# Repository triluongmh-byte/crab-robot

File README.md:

# 🦀 Crab Robot

**An 8-servo crab whose face is a screen with two eyes. Drive it from your phone, or let it walk by itself and dodge obstacles. Play emotions, change the lamp colour.**

[Drive](#open-the-controls) · [Tự đi (Auto)](#tự-đi-auto-mode) · [Gaits](#gaits-and-sliders) · [Emotions](#emotions) · [Calibration](#calibration-ráp) · [Servo channels](#which-servo-goes-where) · [Wiring](#wiring) · [Firmware](#firmware)

| Idle: eyes open, blink, glance | Walking: happy eyes ^ ^ |
|---|---|
|  |  |

*Photos and video by the owner, 14 Nov 2026, firmware `positional180-v19`.*

The web controls are in Vietnamese. Button names below are quoted as they appear on screen, with the English meaning next to them.

## What's on the crab

| Part | How to spot it | Job |
|---|---|---|
| **LILYGO T-Display-S3** (non-touch) | Black board with the screen and USB-C port | Wi-Fi, web controls, the eyes |
| **PCA9685** | Blue board with 16 rows of 3-pin headers | Servo pulses for CH0–CH7 |
| **8 × SG90 positional 180°** | 4 hips on the body, 4 knees on the legs | Joints. **Do not use 360° continuous servos** |
| **WS2812 strip ×8** | Thin strip with 8 LEDs | Colour lamp |
| **2 × HC-SR04P** (round 1, optional) | Two ultrasonic "eyes" at the front | Obstacle sensing for **Tự đi** (Auto) |
| **Separate 5 V servo supply** | Into the PCA `V+` / `GND` screw terminal | Powers servos and LEDs; kept apart from the LILYGO's USB |

## Open the controls

1. Power it on. The servos **arm themselves** one channel at a time over about 3 seconds, then the crab stands up. Keep fingers out from between the legs.
2. Read the **small line at the bottom of the screen**:
   - On home Wi-Fi: the line shows the address, e.g. `Đã vào Wi-Fi  192.168.x.x` ("joined Wi-Fi"). Open that address on a phone on the same network.
   - Not on home Wi-Fi: join the crab's own network **`CuaRobot-XXXX`** (no password) and open **http://192.168.4.1/**.
   - Never saved a Wi-Fi network: the screen shows a QR code to join quickly.
3. Hold a button to walk, release to stop: **↑ Tiến** (forward) · **← Trái** (left) · **Phải →** (right) · **↓ Lùi** (back). If the link drops, the crab stops within 0.5 s.
4. To forget the saved Wi-Fi, hold **BOOT** for about 8 seconds.

On the phone, tap **☰** for settings. The **Trạng thái** (status) tab lists firmware, PCA9685, servos, gait, speed, lamp and Wi-Fi.

## Tự đi (Auto mode)

Needs the two front ultrasonic sensors (round 1 in [firmware/BATTERY-AUTONOMY.md](firmware/BATTERY-AUTONOMY.md)): left on GPIO10/11, right on GPIO12/13.

1. Arm the servos as usual. When both sensors answer, the green **🤖 Tự đi** button above the pad lights up, and the line beside it shows both distances.
2. Tap **🤖 Tự đi**.
   - The crab walks forward and veers away from things on one side.
   - At an obstacle closer than 25 cm it stops with surprised eyes, backs off turning towards the freer side, and carries on.
   - Now and then it wanders off or stops to look around.
3. **DỪNG** or any drive button takes back control (Manual). So do an emotion, **Ráp** and **BOOT**.

It never starts by itself, even after a reset. If it gets stuck 5 times in a row it stops and shows **Kẹt rồi, nhờ giúp** with sad eyes. Locking the phone doesn't stop it; only DỪNG does.

## Gaits and sliders

| Gait | How it moves | When to use it |
|---|---|---|
| **Chéo** (diagonal, default) | Diagonal leg pairs push in turn, with moments where all 4 feet are down | Steady, doesn't spin. The owner's favourite |
| **Cặp trước/sau** (front/rear pairs) | Front pair pushes, then the rear pair | Old gait, kept for comparison. Sideways walking rotates the body |
| **Búng gối** (knee flick, experimental) | Forward/back: hips swing out (front legs forward, rear legs back), then all 4 knees flick. Left/right still uses the diagonal gait | Experiments |

Sliders in the settings panel:

| Slider | Range | Saved on the crab? | Use it when |
|---|---|---|---|
| **Tốc độ** (speed) | 20–100%, default 90% | No (back to 90% at boot) | You want to walk slowly to watch |
| **Độ nhấc gối** (knee lift) | 20–60°, default 45° | Yes | Feet drag on the table while the hips swing back: raise it |
| **Bù lệch trái ↔ phải** (heading trim) | −30 … +30% | Yes | Drifts right walking forward: move towards **+**; drifts left: towards **−** |
| **Góc hông búng** (flick hip angle) | 30–90°, only shown for Búng gối | No | Legs touch each other: lower it |
| **Lamp colour** | Colour picker next to **Bật / tắt đèn** (lamp on/off) | Yes | Changes the LED strip colour |

Angles on the page are **nominal command angles**, not measured ones. On the usual SG90 scale, 1° nominal is about ½° real.

## Emotions

Tap **🎭 Cảm xúc** at the top of the main page, or open `/emo`.

- **7 built-in emotions:** 😄 happy, 😢 sad, 😡 angry, 👋 hello, 💃 dance, 😴 sleep, 😲 surprised. Each has its own lamp colour.
- **Make your own:** drag a leg's Hip/Knee sliders and the crab follows live. Tick **Đối xứng trái/phải** (mirror left/right) to make both sides match. Add frames, set move/hold times, name it and tap **Lưu vào cua** (save to crab).
- **Slider direction:** Hip **+** moves the foot forward. Knee **+** lifts the leg, **−** pushes down (body goes up).
- **Safety:** leaving the page or losing the link returns the crab to its standing pose, slowly at 120°/s.

## The eye screen

Two white eyes on black, drawn from shapes in the style of the Claude pet:

- **Idle:** blinks every 2.5–5.5 s and glances left/right now and then.
- **Walking or playing an emotion:** happy eyes ^ ^.
- **Bottom line:** Wi-Fi state and address on one row. If both don't fit, only the address is shown. PCA9685 wiring errors show here too.

## Calibration (Ráp)

Open **☰ → Ráp** (assembly). Assembly mode locks the drive buttons.

1. Tap **Tư thế đứng** (standing pose).
2. For each hip, tap **±3** until the leg sits at an even diagonal, then fine-tune with **±1**. A ±1 step is close to the SG90 deadband, so the servo may not move on the first tap.
3. For each knee, adjust until all 4 feet touch the floor and the body is level.
4. Tap **Lưu tâm** (save centres), then **Xong ráp** (done). Without Lưu tâm the trims are lost at reboot.

Trims max out at ±30°. If a channel is at ±30°, pull the horn off and refit it one spline over (about 14°) to bring the trim back near 0.

Replacing a servo:
1. Unplug the 5 V supply and remove the horn.
2. Plug it back in, go to **Ráp → Giữa thô · 1500 µs** (rough centre), wait about 3 seconds.
3. Fit the horn so the leg sits on the diagonal.
4. Set that channel's trim back to 0, tune it again, then **Lưu tâm**.

## Which servo goes where?

**One servo = one 3-wire plug = one CH socket.** Hips sit on the body, knees on the legs. Leg names on the Ráp and Cảm xúc pages follow this table:

| Leg | Hip | Knee |
|---|---|---|
| Front left | **CH0** | CH1 |
| Front right | **CH2** | CH3 |
| Rear left | **CH4** | CH5 |
| Rear right | **CH6** | CH7 |

> ⚠️ **Walking direction and leg names are set separately.** The owner turned the crab around, so **Tiến** (forward) walks towards the **CH4/CH6** end (`cfg::FRONT_IS_CH46 = true` in `firmware/crab/config.h`). If forward/back/left/right are all reversed, flip that constant and reflash.

At each socket: **orange → `PWM`/`S`**, **red (middle) → `V+`**, **brown → `GND`/`−`**. Check the GND label printed on the board before plugging in. Leave CH8–CH15 empty.

## Wiring

**Unplug both supplies before changing any wire.**

| Lead | LILYGO pin | Other end |
|---|---|---|
| **A** | `3V` | PCA **`VCC`**, 3.3 V logic |
| **B** | `G` / `GND` | PCA **`GND`** |
| **C** | `18` | PCA **`SDA`** |
| **D** | `17` | PCA **`SCL`** |
| **E** | `1` | LED **`DIN`** |

**Power:**
- **USB:** into the LILYGO's USB-C. Use a data cable when flashing.
- **Separate 5 V:** into the PCA terminal, positive to **`V+`**, negative to **`GND`**.
- **LEDs:** powered from the PCA's servo-side **`V+`/`GND`**.

**`VCC` is 3.3 V logic; `V+` is the 5 V servo supply. Never join them, and never power servos from the LILYGO.** Close-up photos and troubleshooting are in the [wiring guide](firmware/WIRING.md).

## Saving and restoring settings

The owner's tuned settings are in [`firmware/settings/owner-2026-11-13.json`](firmware/settings/owner-2026-11-13.json): trims for all 8 channels, speed, knee lift, heading trim, flick hip angle, gait and lamp colour.

After wiping the flash or swapping the board, restore them with:

```sh
python3 tools/firmware/restore_settings.py firmware/settings/owner-2026-11-13.json --host <crab-ip>
```

Add `--dry-run` to preview the requests. The script needs all 8 servos armed, and it takes control away from any open web page (reload the page afterwards).

## Firmware

- **Running now:** `positional180-v22`, target **`lilygo`**. The **`integrated`** target is for the future integrated board.
- **Build, flash and version history:** [firmware/README.md](firmware/README.md). See also [gaits](firmware/CRAWL.md), [web controls](firmware/WEB-CONTROL.md) and [emotions](firmware/EMOTIONS.md).

```sh
# Host-side tests (don't touch the crab)
python3 tools/firmware/check.py core web drivers display http targets
python3 tools/firmware/test_restore_settings.py

# Build both targets (no flashing, no motors)
python3 tools/firmware/build.py --target all
```

Building doesn't flash a board, run motors, print or order anything.

## Known issues

- **Speed, gait and flick hip angle aren't saved on the crab.** A reboot brings back the defaults: 90%, Chéo, 90°.
- **Walking direction and leg names are set separately** (see the warning under [servo channels](#which-servo-goes-where)). Built-in emotions and the heading trim may feel "back to front" relative to Tiến.
- **A USB cable dragging behind** can pull the crab off course. A power bank mounted on the body walks straighter.
- **Knee flick at 90° goes past the body's old clearance** (30/60°). On the first run, watch for legs hitting each other.

## More docs

| Looking for | Open |
|---|---|
| Printed parts, assembly, body edits | [case/README.md](case/README.md) · [printed parts list](case/PRINTED-INVENTORY.md) |
| Sensors and Auto mode (round 1), battery power (round 2) | [firmware/BATTERY-AUTONOMY.md](firmware/BATTERY-AUTONOMY.md) |
| Integrated ESP32-S3 + PCA9685 board | [docs/INTEGRATED-CONTROLLER.md](docs/INTEGRATED-CONTROLLER.md) · [KiCad sources](design/) |
| Build-from-source results | [BUILD-VALIDATION.md](BUILD-VALIDATION.md) |
| 360° servo trials (didn't work out) | [firmware/EXPERIMENT-STATUS.md](firmware/EXPERIMENT-STATUS.md) |

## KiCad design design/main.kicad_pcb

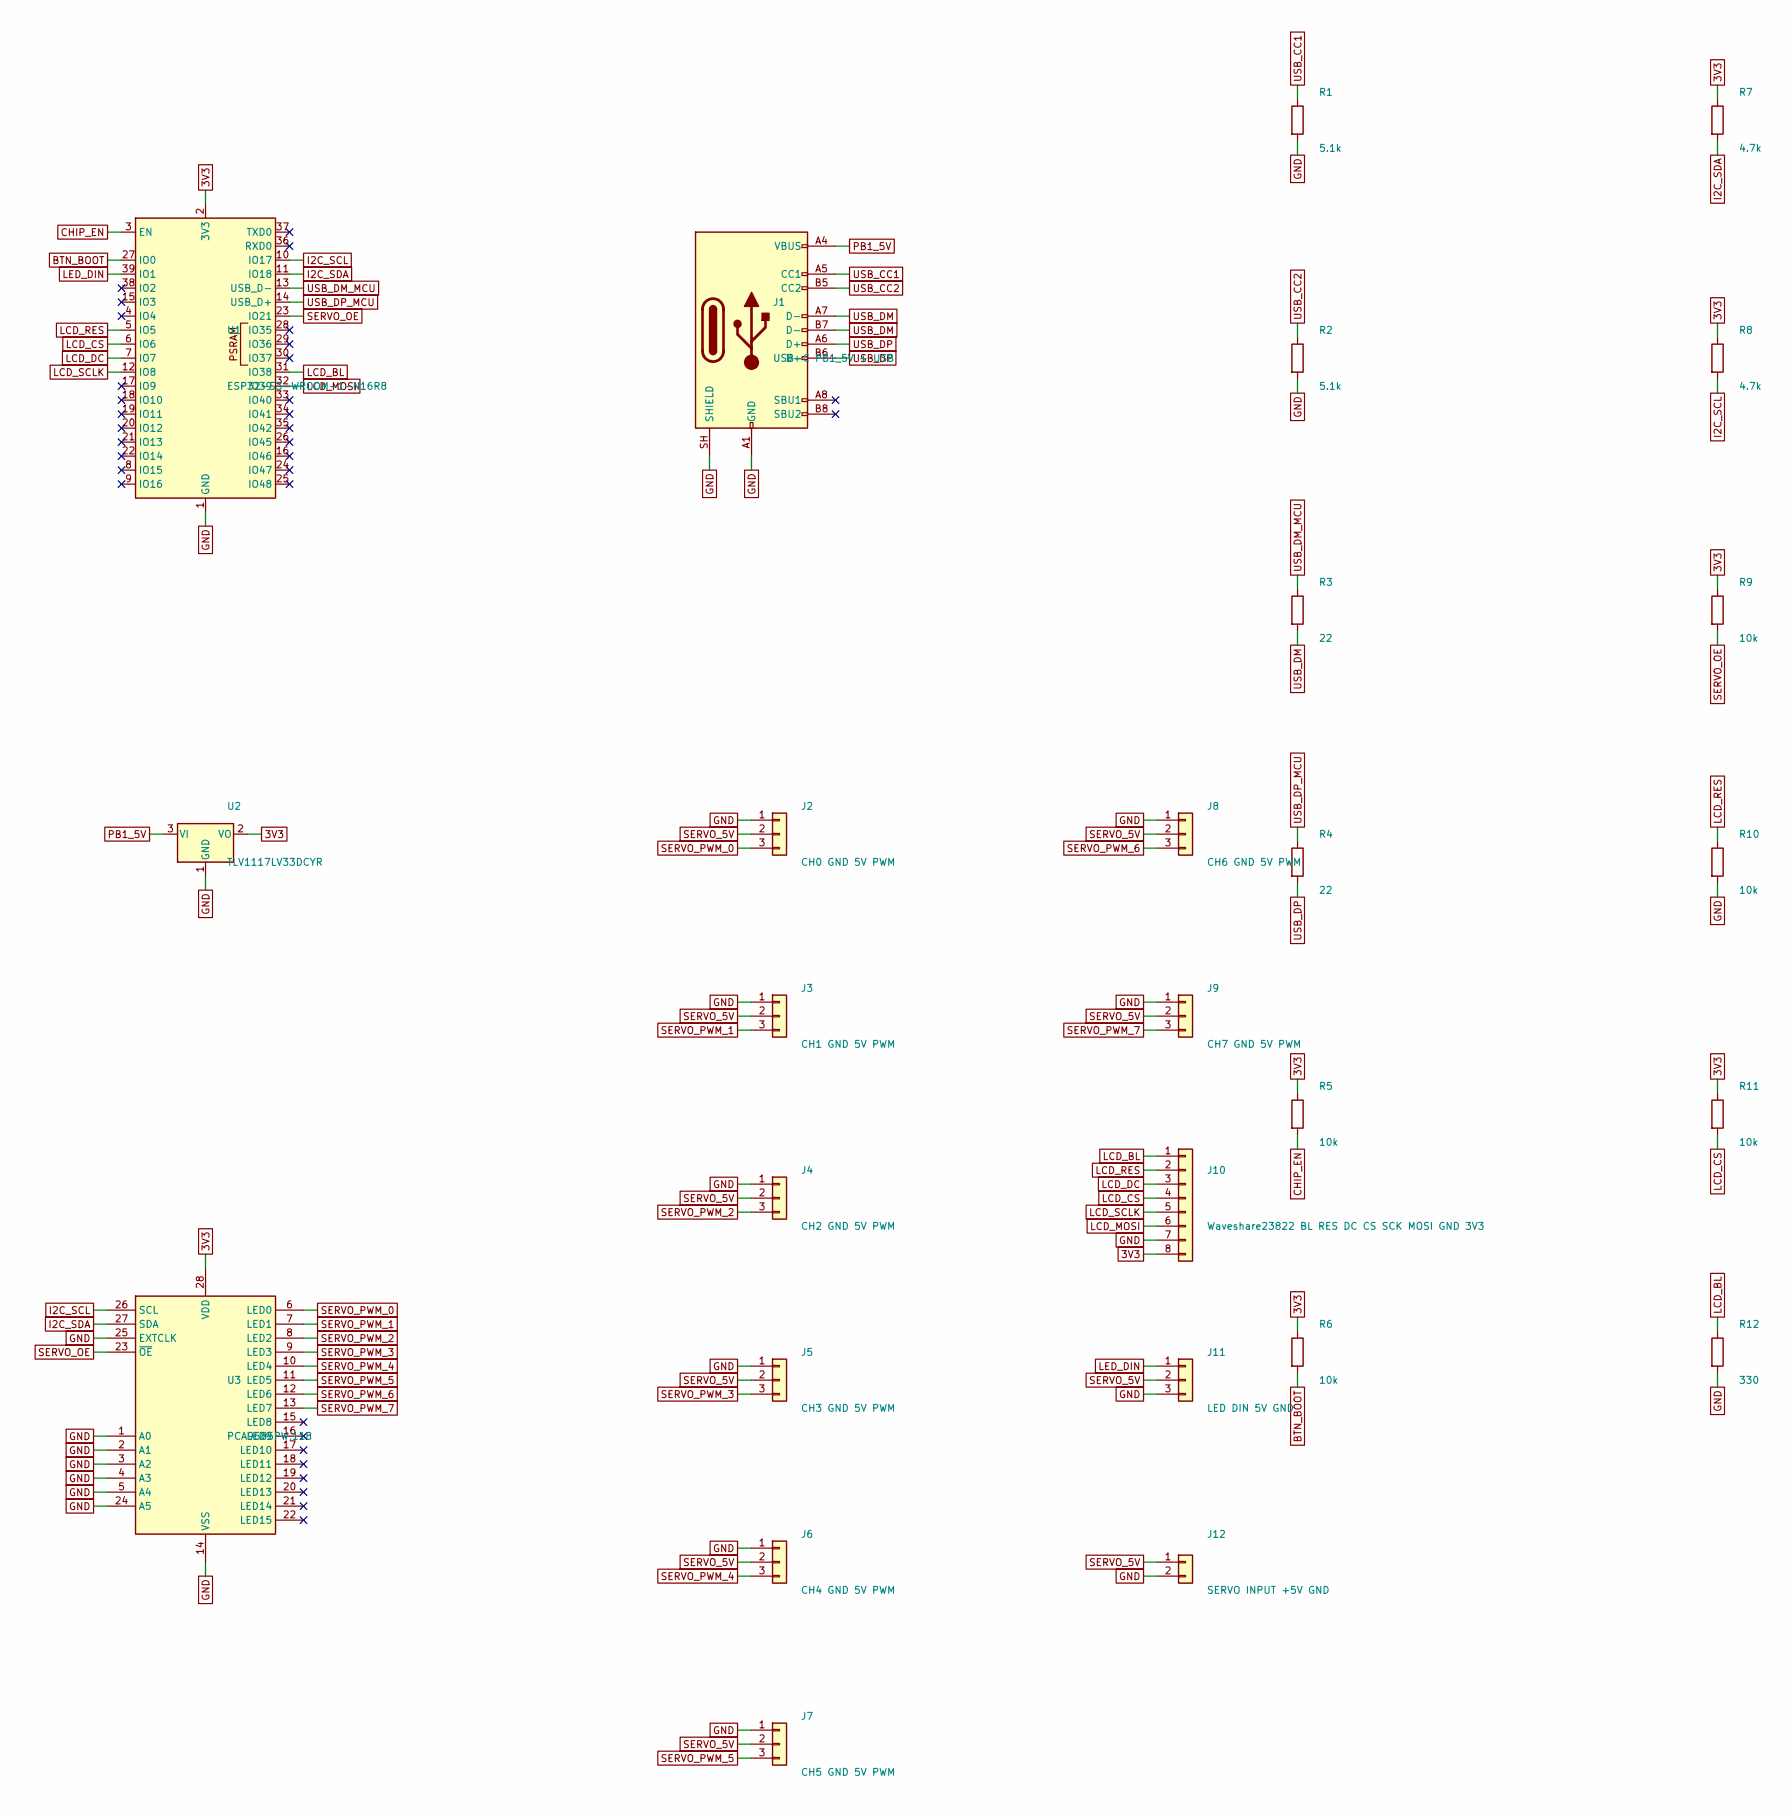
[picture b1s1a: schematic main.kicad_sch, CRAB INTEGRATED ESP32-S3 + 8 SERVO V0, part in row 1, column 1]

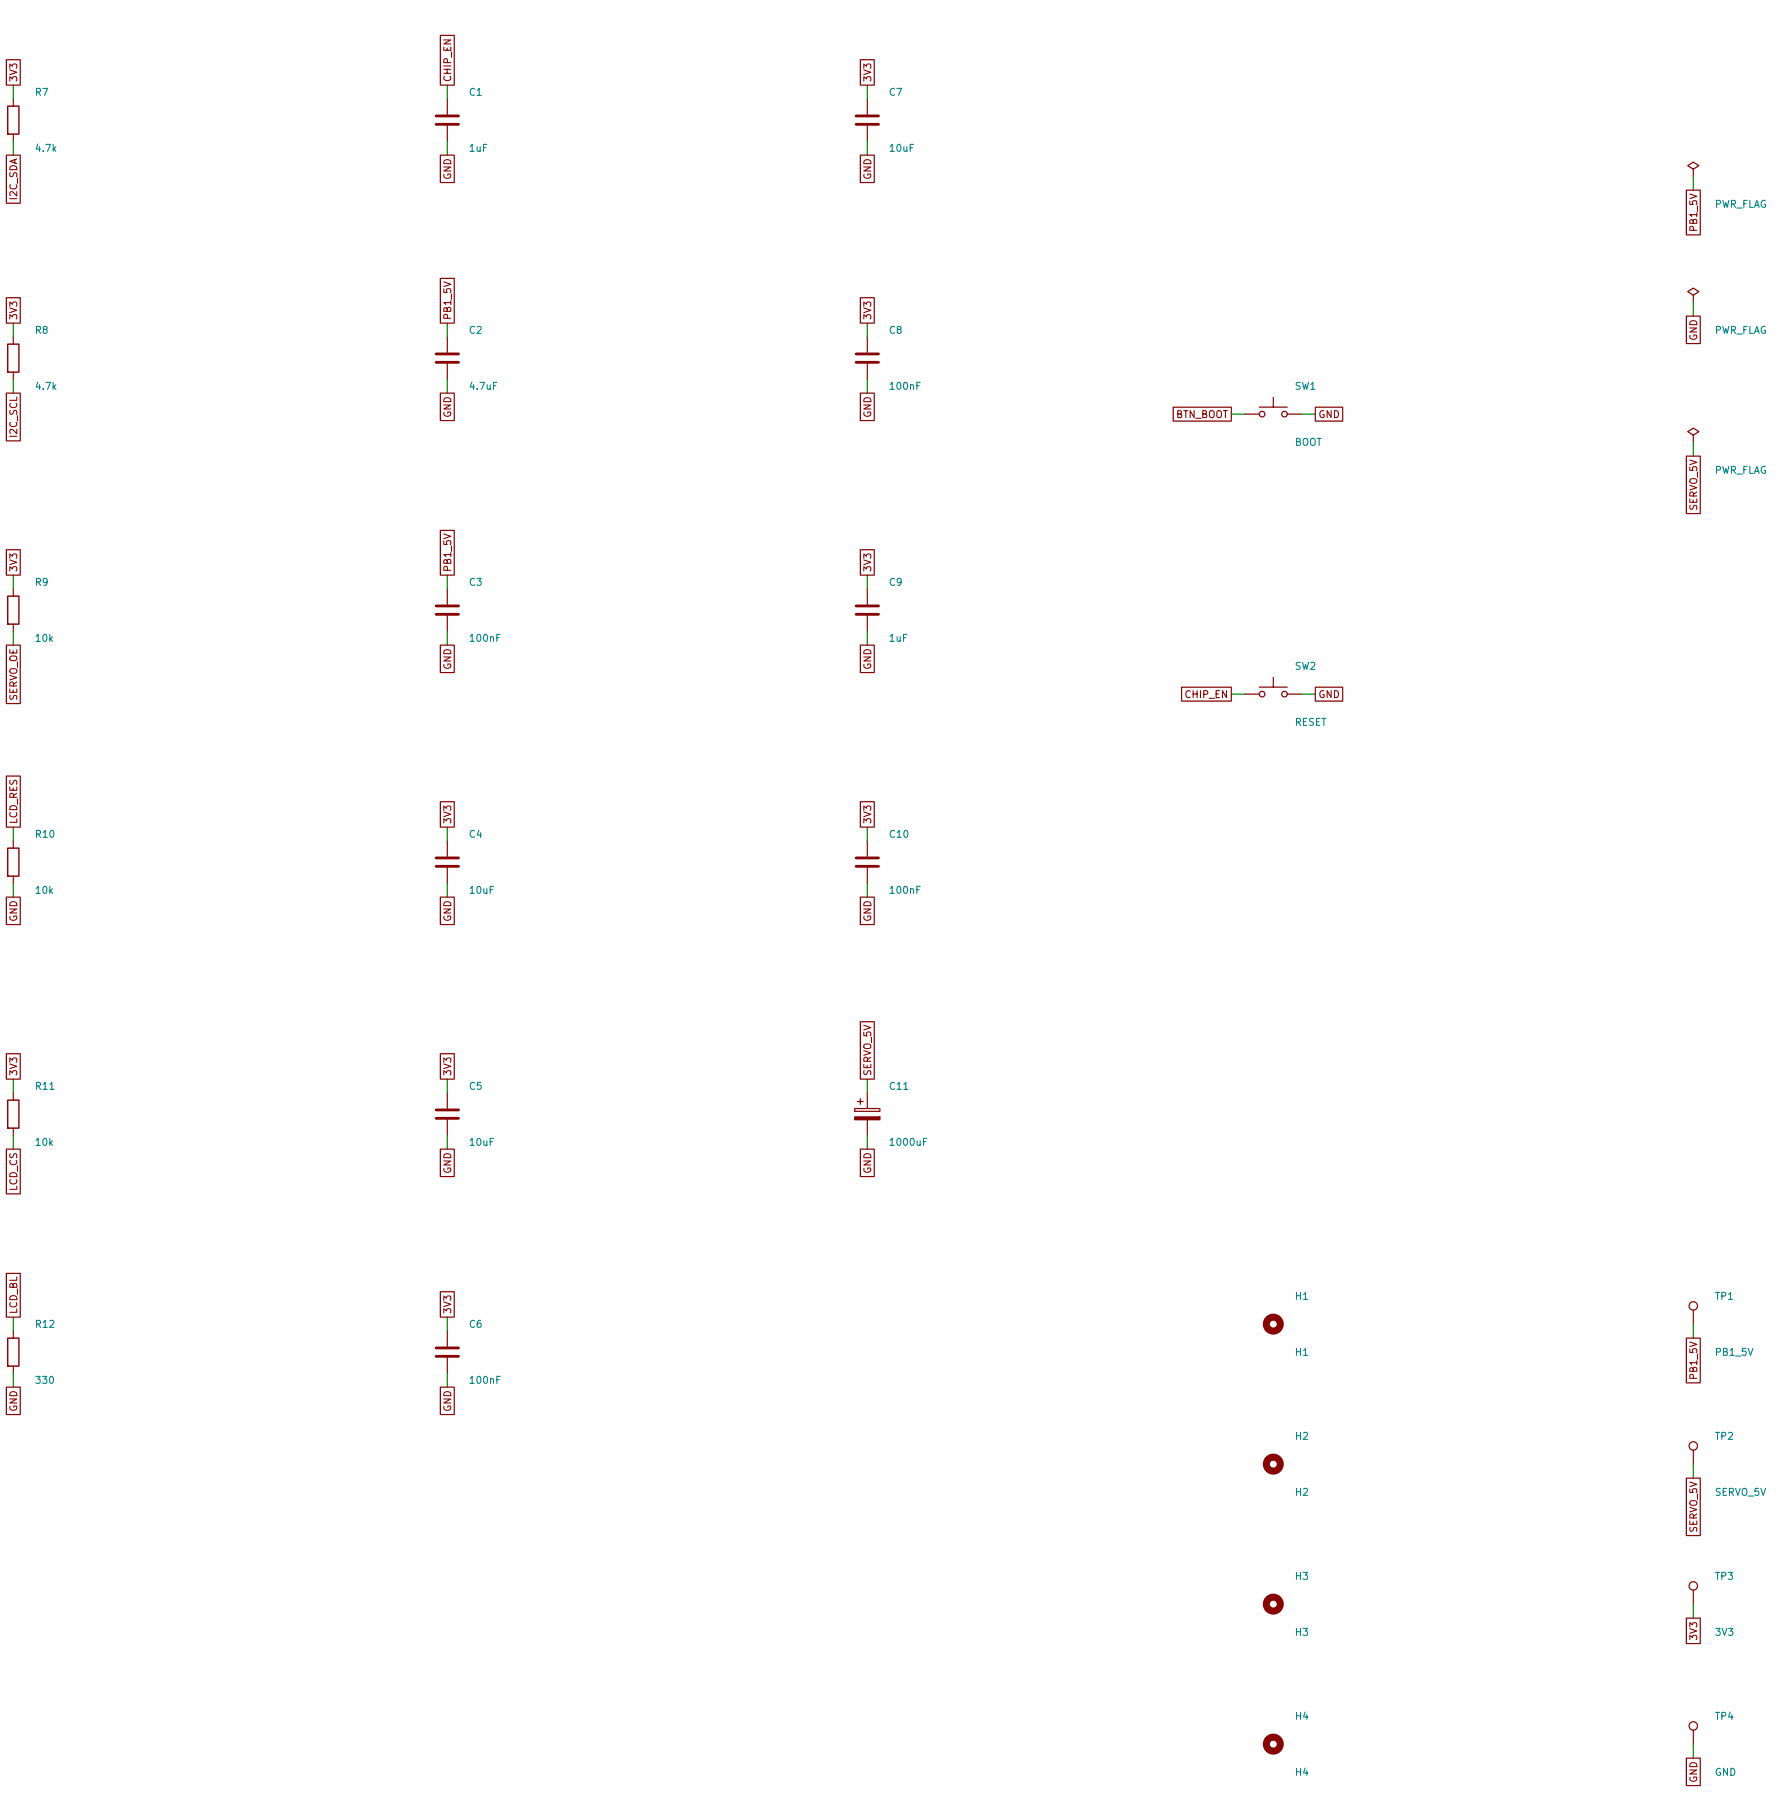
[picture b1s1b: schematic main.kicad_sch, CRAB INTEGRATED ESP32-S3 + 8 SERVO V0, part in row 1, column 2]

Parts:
C1, C9: 1uF; C_0402_1005Metric
C2: 4.7uF; C_0805_2012Metric
C3, C6, C8, C10: 100nF; C_0402_1005Metric
C4, C5, C7: 10uF; C_0805_2012Metric
C11: 1000uF; CP_Elec_10x10
H1: H1; MountingHole_3.2mm_M3
H2: H2; MountingHole_3.2mm_M3
H3: H3; MountingHole_3.2mm_M3
H4: H4; MountingHole_3.2mm_M3
J1: USB-C PB1_5V + USB; USB_C_Receptacle_HRO_TYPE-C-31-M-12
J2: CH0 GND 5V PWM; PinHeader_1x03_P2.54mm_Vertical
J3: CH1 GND 5V PWM; PinHeader_1x03_P2.54mm_Vertical
J4: CH2 GND 5V PWM; PinHeader_1x03_P2.54mm_Vertical
J5: CH3 GND 5V PWM; PinHeader_1x03_P2.54mm_Vertical
J6: CH4 GND 5V PWM; PinHeader_1x03_P2.54mm_Vertical
J7: CH5 GND 5V PWM; PinHeader_1x03_P2.54mm_Vertical
J8: CH6 GND 5V PWM; PinHeader_1x03_P2.54mm_Vertical
J9: CH7 GND 5V PWM; PinHeader_1x03_P2.54mm_Vertical
J10: Waveshare23822 BL RES DC CS SCK MOSI GND 3V3; PinHeader_1x08_P2.54mm_Vertical
J11: LED DIN 5V GND; PinHeader_1x03_P2.54mm_Vertical
J12: SERVO INPUT +5V GND; TerminalBlock_Phoenix_MKDS-1,5-2-5.08_1x02_P5.08mm_Horizont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
R1, R2: 5.1k; R_0402_1005Metric
R3, R4: 22; R_0402_1005Metric
R5, R6, R9, R10, R11: 10k; R_0402_1005Metric
R7, R8: 4.7k; R_0402_1005Metric
R12: 330; R_0402_1005Metric
SW1: BOOT; SW_Push_1P1T_XKB_TS-1187A
SW2: RESET; SW_Push_1P1T_XKB_TS-1187A
TP1: PB1_5V; TestPoint_Pad_D2.0mm
TP2: SERVO_5V; TestPoint_Pad_D2.0mm
TP3: 3V3; TestPoint_Pad_D2.0mm
TP4: GND; TestPoint_Pad_D2.0mm
U1: ESP32-S3-WROOM-1-N16R8; ESP32-S3-WROOM-1
U2: TLV1117LV33DCYR; SOT-223-3_TabPin2
U3: PCA9685PW,118; TSSOP-28_4.4x9.7mm_P0.65mm

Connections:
3V3: C4.1, C5.1, C6.1, C7.1, C8.1, C9.1, C10.1, J10.8, R5.1, R6.1, R7.1, R8.1, R9.1, R11.1, TP3.1, U1.2 (3V3), U2.2 (VO), U3.28 (VDD)
BTN_BOOT: R6.2, SW1.1, U1.27 (IO0)
CHIP_EN: C1.1, R5.2, SW2.1, U1.3 (EN)
GND: C1.2, C2.2, C3.2, C4.2, C5.2, C6.2, C7.2, C8.2, C9.2, C10.2, C11.2, J1.A1 (GND), J1.A12 (GND), J1.B1 (GND), J1.B12 (GND), J1.SH (SHIELD), J2.1, J3.1, J4.1, J5.1, J6.1, J7.1, J8.1, J9.1, J10.7, J11.3, J12.2, R1.2, R2.2, R10.2, R12.2, SW1.2, SW2.2, TP4.1, U1.1 (GND), U1.40 (GND), U1.41 (GND), U2.1 (GND), U3.1 (A0), U3.2 (A1), U3.3 (A2), U3.4 (A3), U3.5 (A4), U3.14 (VSS), U3.24 (A5), U3.25 (EXTCLK)
I2C_SCL: R8.2, U1.10 (IO17), U3.26 (SCL)
I2C_SDA: R7.2, U1.11 (IO18), U3.27 (SDA)
LCD_BL: J10.1, R12.1, U1.31 (IO38)
LCD_CS: J10.4, R11.2, U1.6 (IO6)
LCD_DC: J10.3, U1.7 (IO7)
LCD_MOSI: J10.6, U1.32 (IO39)
LCD_RES: J10.2, R10.1, U1.5 (IO5)
LCD_SCLK: J10.5, U1.12 (IO8)
LED_DIN: J11.1, U1.39 (IO1)
PB1_5V: C2.1, C3.1, J1.A4 (VBUS), J1.A9 (VBUS), J1.B4 (VBUS), J1.B9 (VBUS), TP1.1, U2.3 (VI)
SERVO_5V: C11.1, J2.2, J3.2, J4.2, J5.2, J6.2, J7.2, J8.2, J9.2, J11.2, J12.1, TP2.1
SERVO_OE: R9.2, U1.23 (IO21), U3.23 (~OE)
SERVO_PWM_0: J2.3, U3.6 (LED0)
SERVO_PWM_1: J3.3, U3.7 (LED1)
SERVO_PWM_2: J4.3, U3.8 (LED2)
SERVO_PWM_3: J5.3, U3.9 (LED3)
SERVO_PWM_4: J6.3, U3.10 (LED4)
SERVO_PWM_5: J7.3, U3.11 (LED5)
SERVO_PWM_6: J8.3, U3.12 (LED6)
SERVO_PWM_7: J9.3, U3.13 (LED7)
USB_CC1: J1.A5 (CC1), R1.1
USB_CC2: J1.B5 (CC2), R2.1
USB_DM: J1.A7 (D-), J1.B7 (D-), R3.2
USB_DM_MCU: R3.1, U1.13 (USB_D-)
USB_DP: J1.A6 (D+), J1.B6 (D+), R4.2
USB_DP_MCU: R4.1, U1.14 (USB_D+)

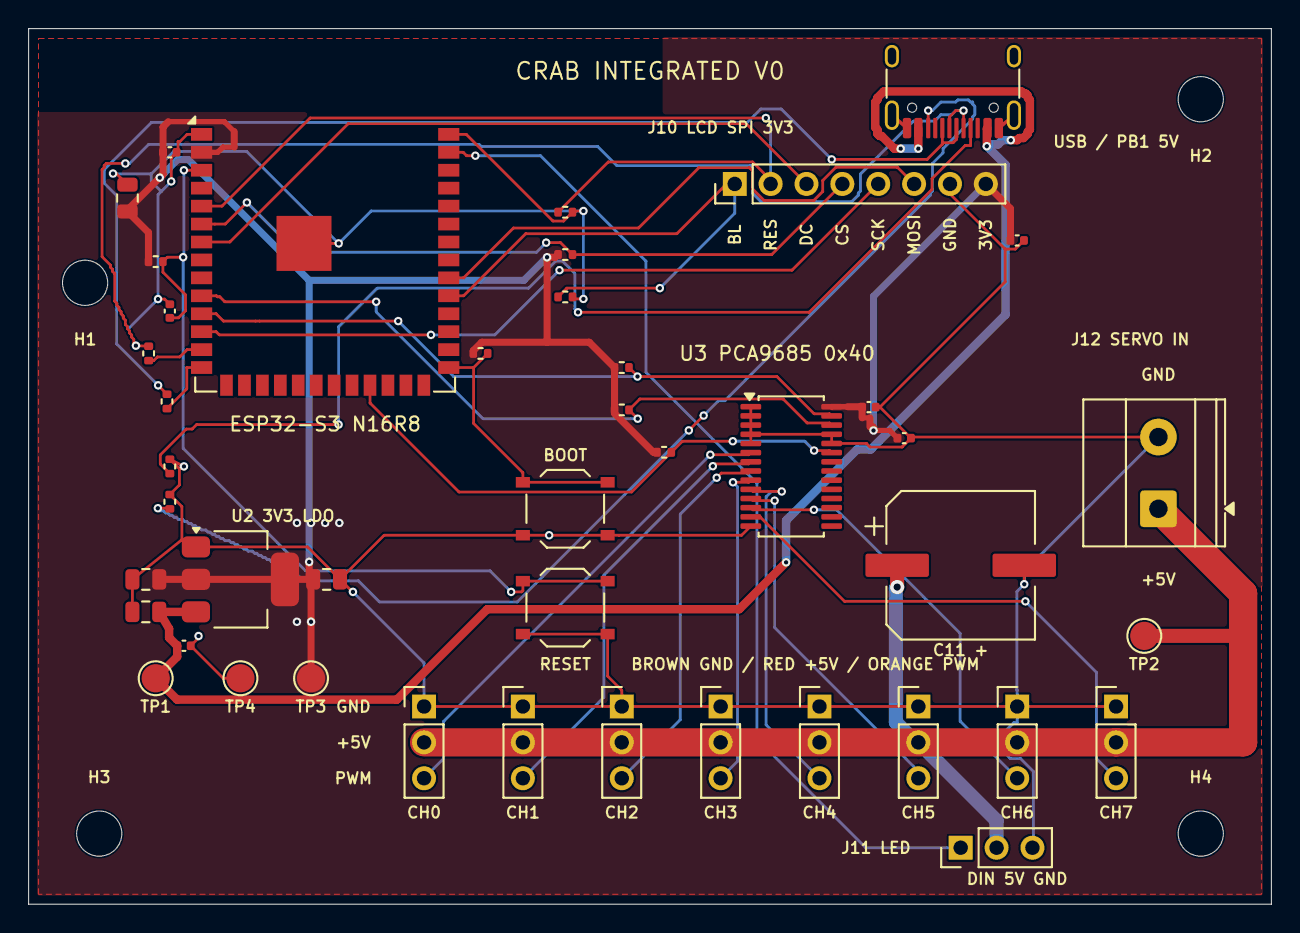
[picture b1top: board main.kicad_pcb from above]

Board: 2 copper layers, 88.0 x 62.0 mm, 48 parts (0 on the bottom side), 30 nets.

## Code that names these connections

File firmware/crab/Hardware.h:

#pragma once
// Select at compile time; never detect/remap hardware from a running device.
#ifndef CRAB_INTEGRATED_BOARD
#define CRAB_INTEGRATED_BOARD 0
#endif
#if CRAB_INTEGRATED_BOARD != 0 && CRAB_INTEGRATED_BOARD != 1
#error "CRAB_INTEGRATED_BOARD must be 0 (LILYGO) or 1 (integrated)"
#endif
namespace cfg {
constexpr bool INTEGRATED_BOARD=CRAB_INTEGRATED_BOARD;
constexpr int SDA_PIN=18, SCL_PIN=17, LED_PIN=1, BOOT_PIN=0;
constexpr int USB_DM=19, USB_DP=20;
constexpr int LCD_BL=38, LCD_RST=5, LCD_CS=6, LCD_DC=7;
#if CRAB_INTEGRATED_BOARD
// Final U1.23 -> U3.23, R9 10k to 3V3. GPIO15 is physically NC.
constexpr int POWER_PIN=-1, PCA_OE_PIN=21;
constexpr bool LCD_SPI=true;
constexpr int LCD_SCLK=8, LCD_MOSI=39, LCD_SPI_HZ=10000000;
constexpr int LCD_WR=-1, LCD_RD=-1, LCD_DATA[8]={-1,-1,-1,-1,-1,-1,-1,-1};
constexpr int LCD_ROTATION_DEG=270; // vendor landscape 90 + case D15 180
constexpr const char* HARDWARE_TARGET="integrated";
#else
constexpr int POWER_PIN=15, PCA_OE_PIN=-1;
constexpr bool LCD_SPI=false;
constexpr int LCD_SCLK=-1, LCD_MOSI=-1, LCD_SPI_HZ=0;
constexpr int LCD_WR=8, LCD_RD=9, LCD_DATA[8]={39,40,41,42,45,46,47,48};
constexpr int LCD_ROTATION_DEG=90;
constexpr const char* HARDWARE_TARGET="lilygo";
#endif
constexpr bool LCD_NEW_PANEL=true; // LILYGO factory only; integrated uses Waveshare init
}
